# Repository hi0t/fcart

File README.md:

# Open source flash cartridge for FC

**⚠️ This project is currently in active development stage**

## Hardware Features

- **8MB SDRAM** - Single SDRAM module for loading both PRG and CHR data with fast access and execution
- **MachXO2 FPGA** - Main logic implemented in Lattice MachXO2 FPGA
- **ARM processor** - Dedicated ARM processor handles ROM loading from SD card and system management
- **Expansion Audio** - Additional sound support powered by an onboard Op-Amp
- **RTC Battery** - Onboard battery for Real-Time Clock support
- **Simple PCB design** - Circuit design optimized for hand assembly and DIY builds
- **USB programming port** - USB interface for firmware updates

## Software Features

- **Game loading from SD card** - Fast ROM loading and execution directly from SD card storage (supports FAT16, FAT32, and exFAT)
- **In-game menu** - Access save states and return to the main menu without resetting the console
- **Save states** - Save and load game progress at any point during gameplay
- **Battery-backed RAM** - Saving backed RAM to flash storage automatically when entering the in-game menu or resetting the console
- **Alphabetical sorting** - Automatic alphabetical sorting of files and folders in the file browser

## Getting Started

1. **Flash the bootloader**: First, you need to flash the bootloader to the cartridge using the project's [GitHub Pages site](https://hi0t.github.io/fcart/).
2. **Install/Update Firmware**: With the SD card removed, connect the cartridge via USB. It will boot into bootloader mode and appear as a USB drive named `FCART BOOT`. Download the latest `fcart.uf2` firmware file from the [Releases page](https://github.com/hi0t/fcart/releases) and copy it to this drive.
3. **Ready to play**: Insert your SD card with ROMs, plug the cartridge into your console, and it's ready to use!

## Manufacturing (PCB)

**Ordering Specifications:**
- **Thickness:** 1.2 mm
- **Surface Finish:** **ENIG** (Electroless Nickel Immersion Gold) is recommended. While this finish is more expensive than standard HASL, it provides significantly better durability.
- **Edge Connector:** **Gold Fingers** (make sure to specify this option even if ENIG is selected).
- **Gold Fingers Bevel:** **45° Bevel** (Chamfer). This ensures smooth and safe repeated insertions into the console.

**Production Files:**
- 🗺️ [Interactive HTML BOM (iBOM)](https://hi0t.github.io/fcart/board/fcart-ibom.html) - Convenient interactive map for hand assembly.
- 📄 [BOM (CSV)](https://hi0t.github.io/fcart/board/fcart-bom.csv) - Bill of Materials in CSV format (includes DigiKey and LCSC part numbers).
- 📦 [Gerbers & Drills (ZIP)](https://hi0t.github.io/fcart/board/fcart-gerbers.zip) - Ready-to-order manufacturing archive.

## Supported Mappers

| | +0 | +1 | +2 | +3 | +4 | +5 | +6 | +7 | +8 | +9 |
|---|:---:|:---:|:---:|:---:|:---:|:---:|:---:|:---:|:---:|:---:|
| **00** | NROM | MMC1B | UxROM | CNROM | MMC3 | | | AxROM | | |
| **10** | | | | | | | | | | |
| **20** | | VRC4a | VRC2a | VRC2b | VRC6a | VRC4b | VRC6b | VRC4 | | |
| **30** | | | | | | | | | | |
| **40** | | | | | | | | | | |
| **50** | | | | | | | | | | |
| **60** | | | | | | | | | | FME7 |
| **70** | | | | | | | | | | |
| **80** | | | | | | | | | | |
| **90** | | | | | UN1ROM | | | | | |
| **100** | | | | | | | | | | |
| **110** | | | | | | | | | | |
| **120** | | | | | | | | | | |
| **130** | | | | | | | | | | |
| **140** | | | | | | | | | | |
| **150** | | | | | | MMC1A | | | | |
| **160** | | | | | | | | | | |
| **170** | | KS7058 | | | | | | | | |
| **180** | UNROM | | | | | CNROM | | | | |
| **190** | | | | | | | | | | |
| **200** | | | | | | | | | | |
| **210** | | | | | | | | | | |
| **220** | | | | | | | | | | |
| **230** | | | | | | | | | | |
| **240** | | | | | | | | | | |
| **250** | | | | | | | | | | |

## Planned Features

- [ ] **Extended mapper support** - Adding support for a larger number of mappers to increase game compatibility
- [ ] **FDS support** - Support for loading FDS disk images

## Photos

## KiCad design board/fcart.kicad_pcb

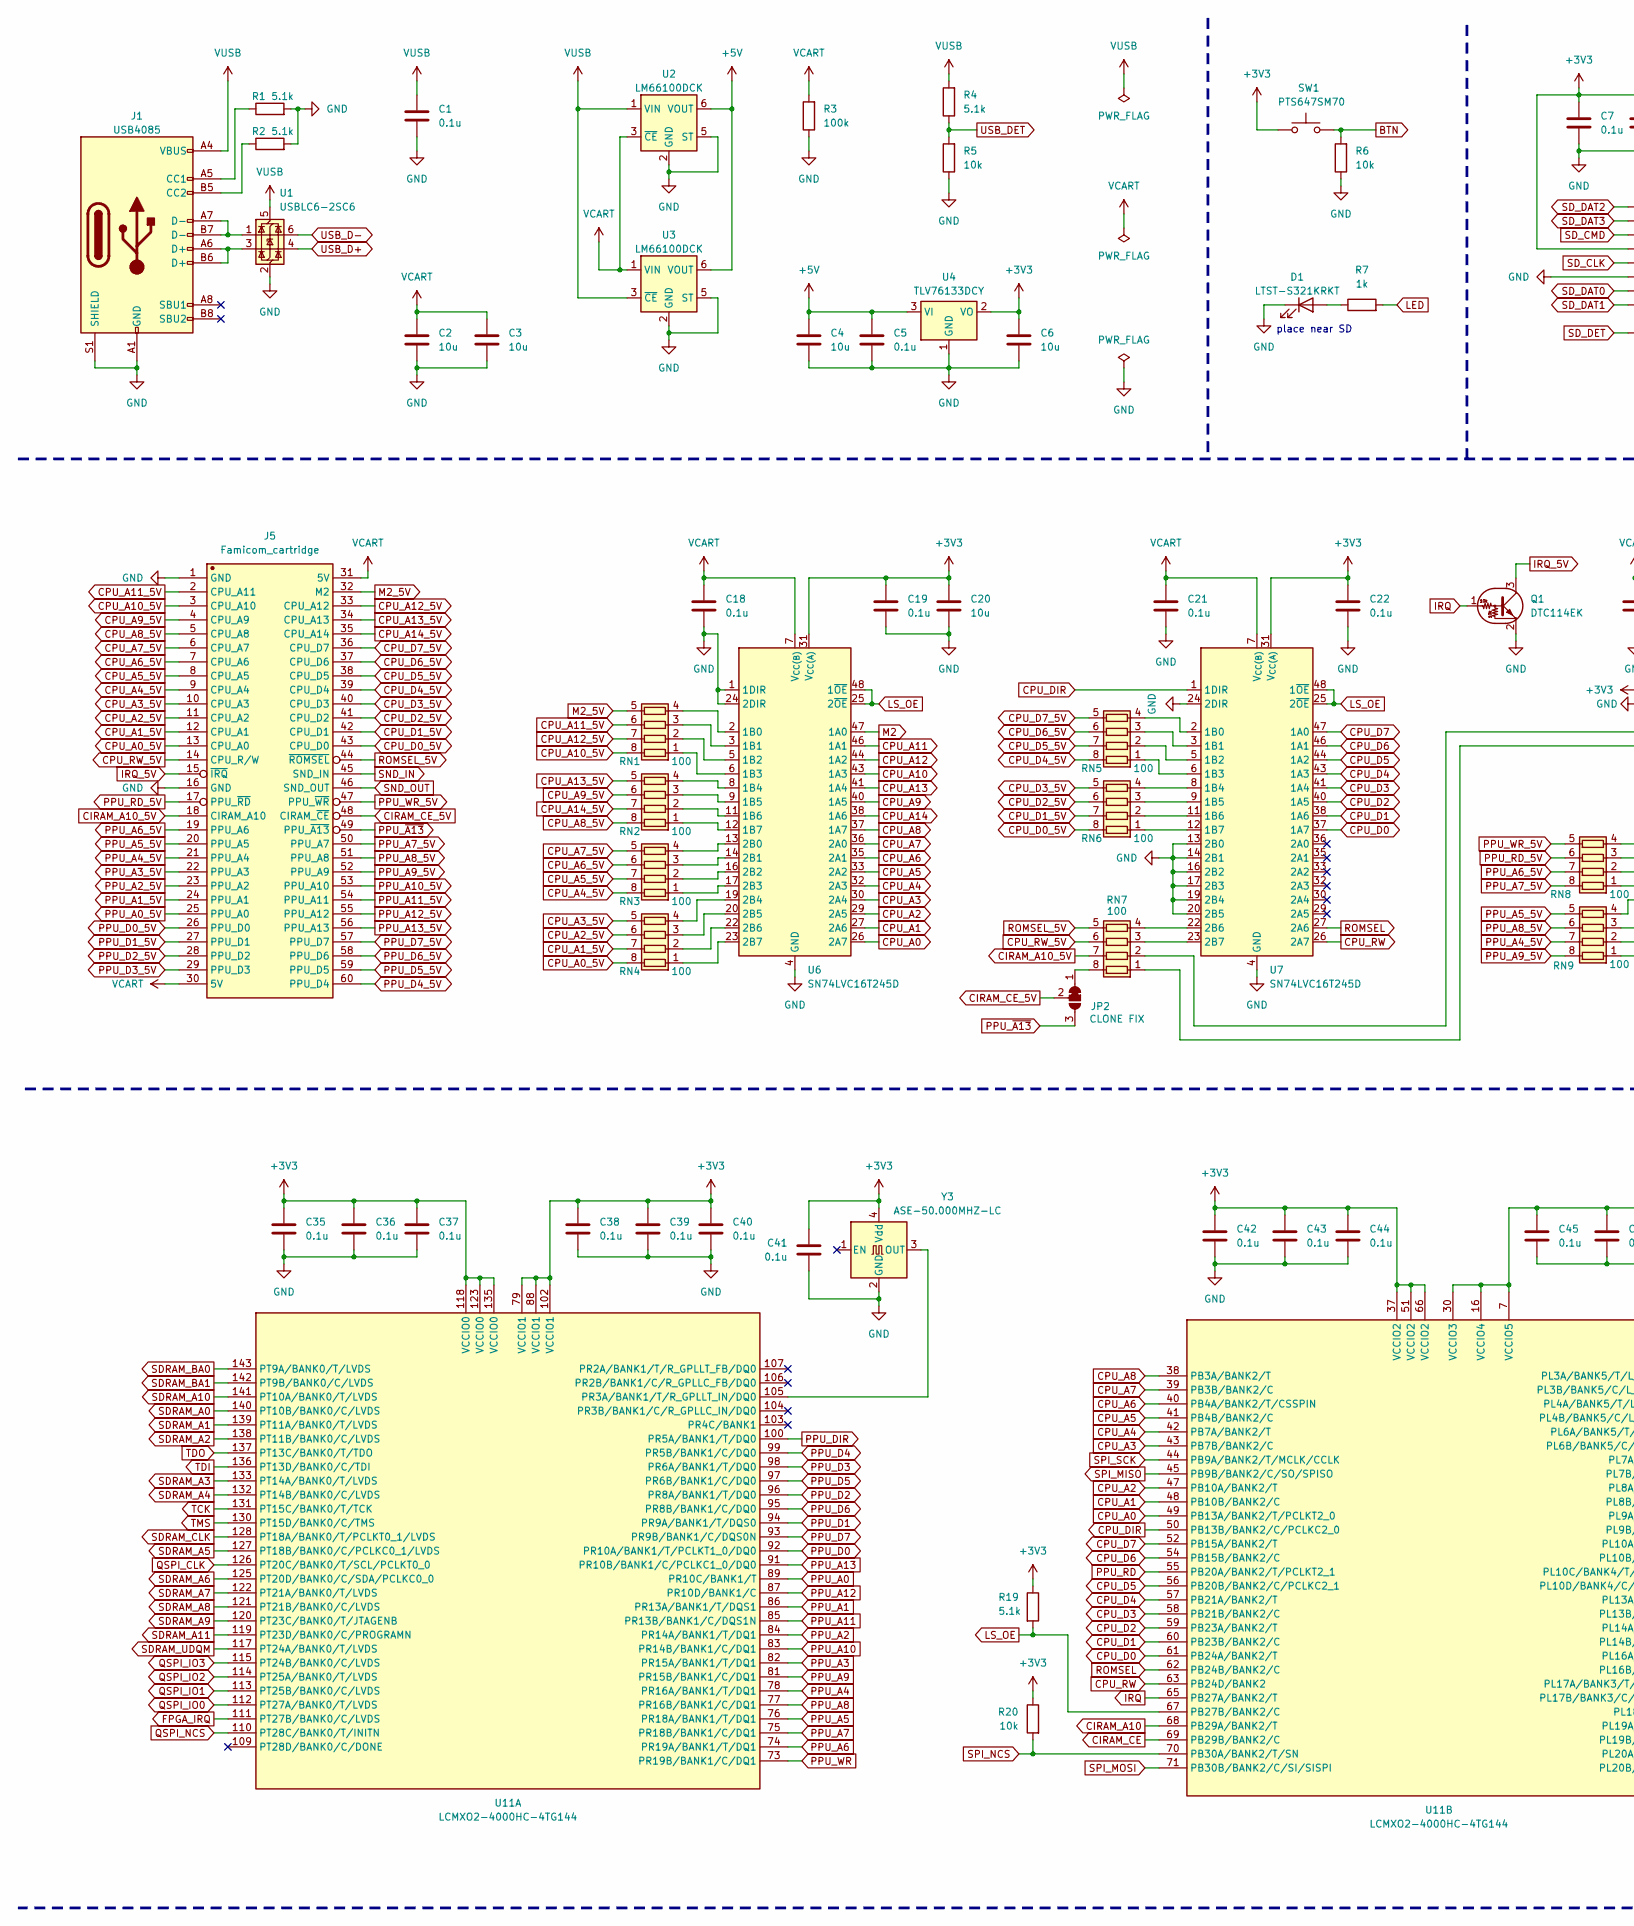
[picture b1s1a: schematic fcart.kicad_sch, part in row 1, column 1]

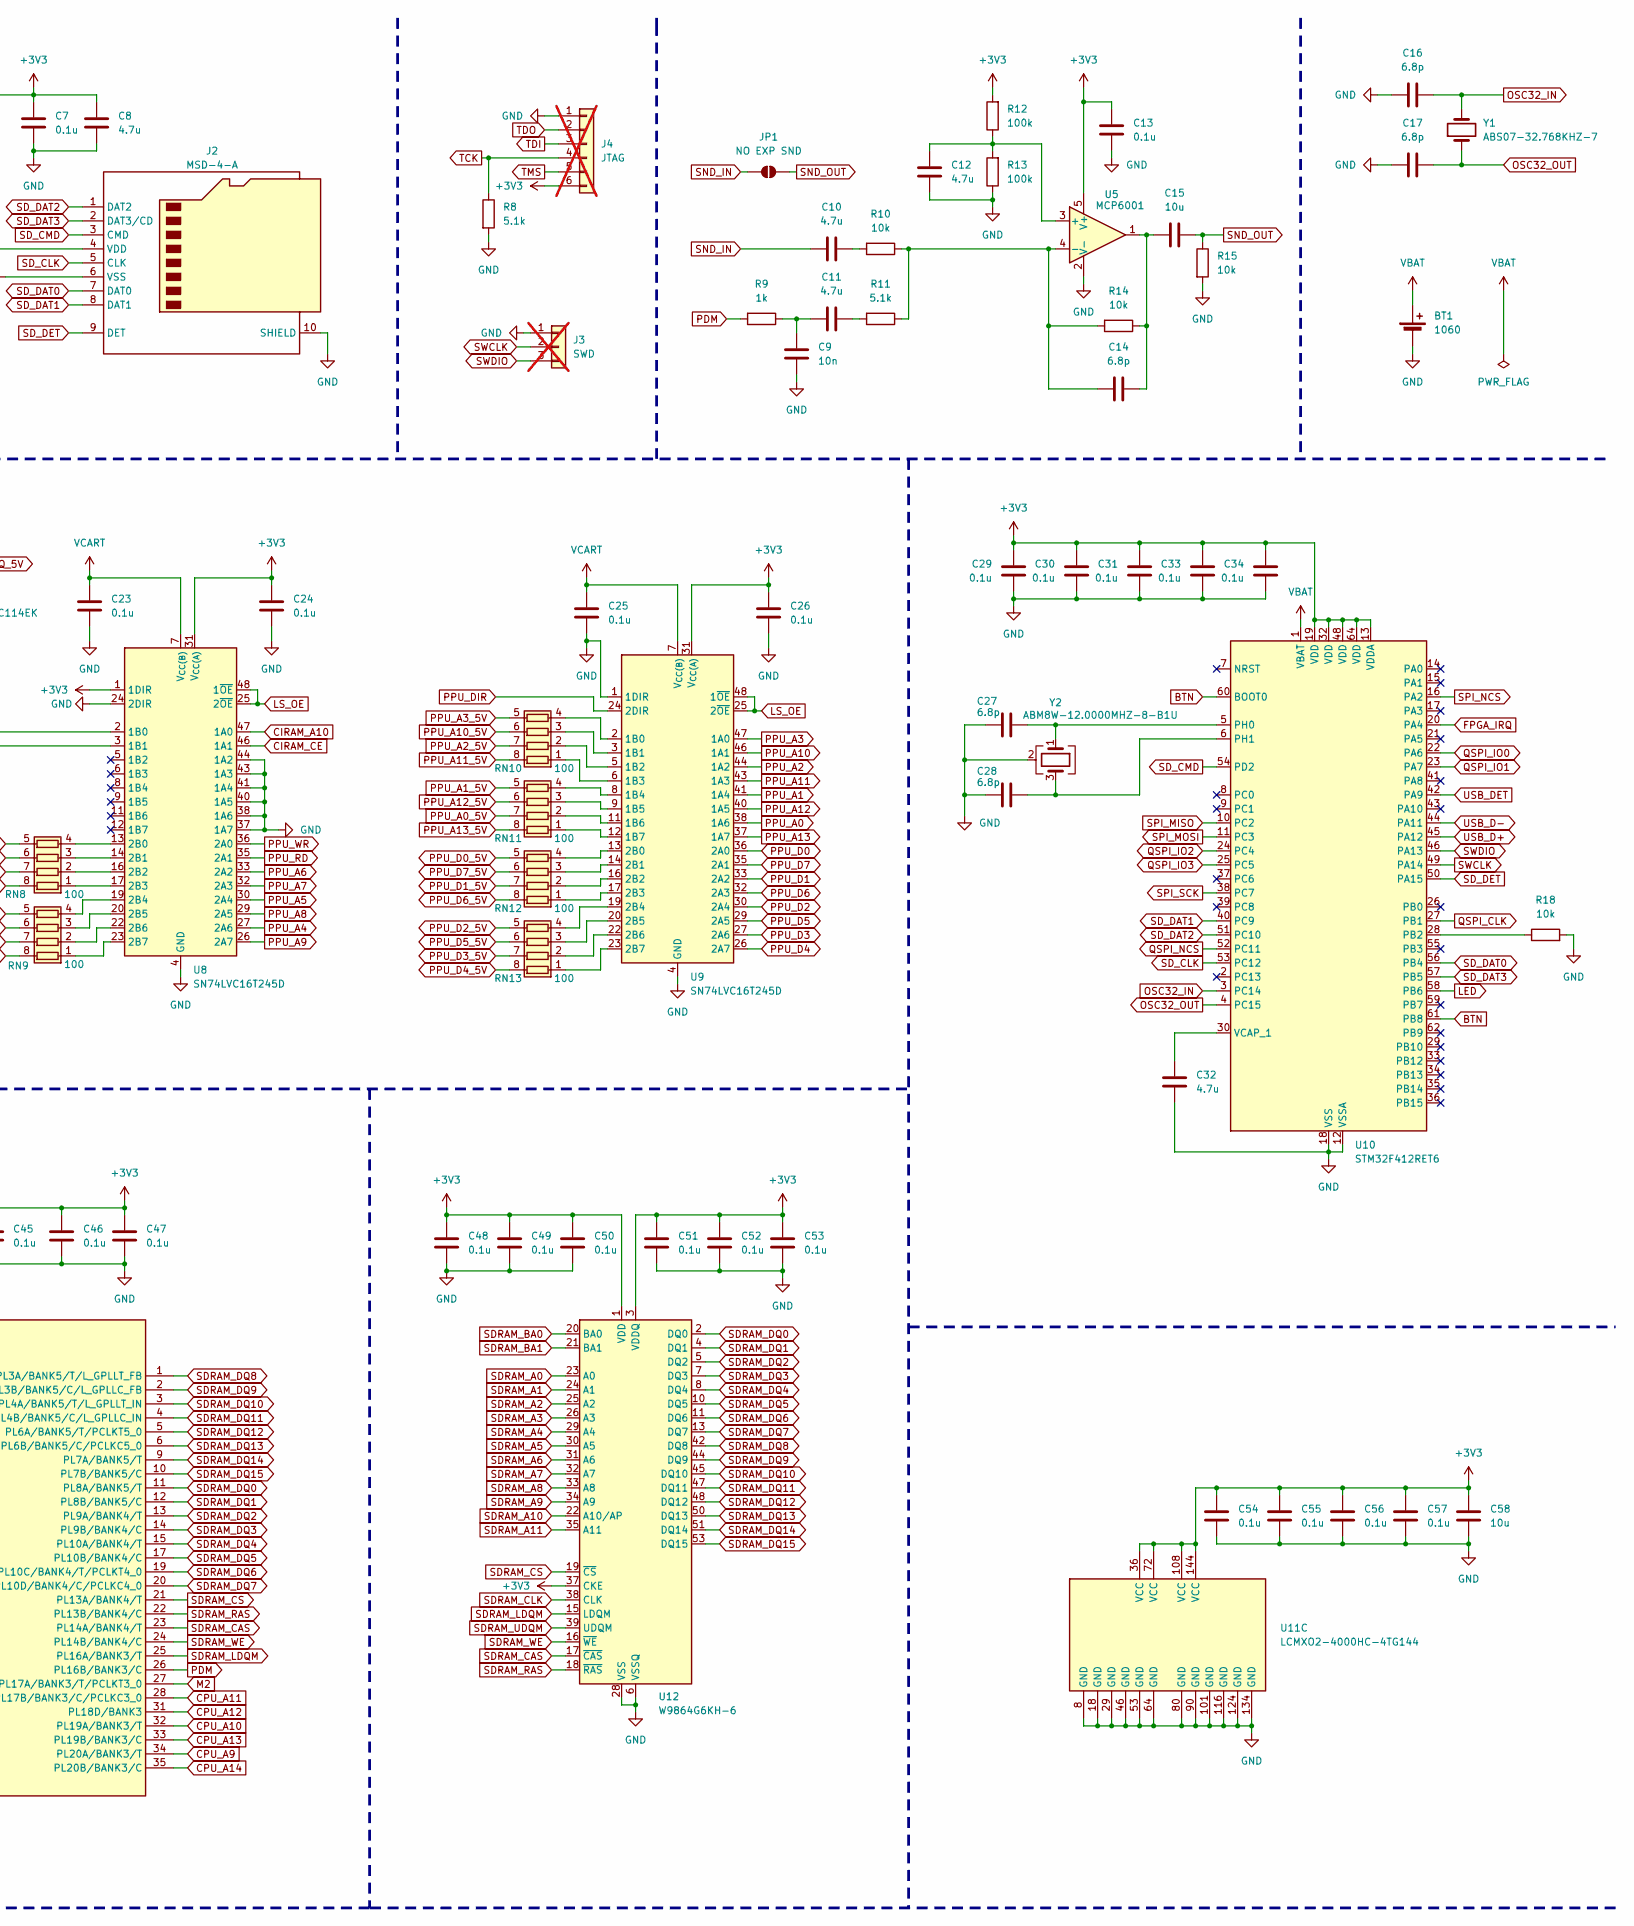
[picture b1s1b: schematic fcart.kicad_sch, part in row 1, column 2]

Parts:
BT1: 1060; BatteryHolder_Keystone_1060_1x2032
C1, C5, C7, C13, C18, C19, C21, C22, C23, C24, C25, C26, C29, C30, C31, C33, C34, C35, C36, C37, C38, C39, C40, C41, C42, C43, C44, C45, C46, C47, C48, C49, C50, C51, C52, C53, C54, C55, C56, C57: 0.1u; C_0805_2012Metric
C2, C3, C4, C6, C15, C20, C58: 10u; C_0805_2012Metric
C8, C10, C11, C12, C32: 4.7u; C_0805_2012Metric
C9: 10n; C_0805_2012Metric
C14, C16, C17, C27, C28: 6.8p; C_0805_2012Metric
D1: LTST-S321KRKT; LED_1208_Horizontal_3210Metric
J1: USB4085; USB_C_Receptacle_GCT_USB4085
J2: MSD-4-A; microSD_HC_Same_Sky_MSD-4-A
J3: SWD; PinHeader_1x03_P2.54mm_Vertical; not fitted
J4: JTAG; PinHeader_1x06_P2.54mm_Vertical; not fitted
J5: Famicom_cartridge; Famicom cartridge pcb
JP1: NO EXP SND; SolderJumper-2_P1.3mm_Open_RoundedPad1.0x1.5mm
JP2: CLONE FIX; SolderJumper-3_P1.3mm_Bridged12_RoundedPad1.0x1.5mm
Q1: DTC114EK; SOT-23-3
R1, R2, R4, R8, R11, R19: 5.1k; R_0805_2012Metric
R3, R12, R13: 100k; R_0805_2012Metric
R5, R6, R10, R14, R15, R18, R20: 10k; R_0805_2012Metric
R7, R9: 1k; R_0805_2012Metric
RN1, RN2, RN3, RN4, RN5, RN6, RN7, RN8, RN9, RN10, RN11, RN12, RN13: 100; R_Array_Convex_4x0603
SW1: PTS647SM70; SW_SPST_PTS647_Sx70
U1: USBLC6-2SC6; SOT-23-6
U2, U3: LM66100DCK; SOT-363_SC-70-6
U4: TLV76133DCY; SOT-223-3_TabPin2
U5: MCP6001; SOT-23-5
U6, U7, U8, U9: SN74LVC16T245D; TSSOP-48_6.1x12.5mm_P0.5mm
U10: STM32F412RET6; LQFP-64_10x10mm_P0.5mm
U11: LCMXO2-4000HC-4TG144; TQFP-144_20x20mm_P0.5mm
U12: W9864G6KH-6; TSOP-II-54_22.2x10.16mm_P0.8mm
Y1: ABS07-32.768KHZ-7; Crystal_SMD_3215-2Pin_3.2x1.5mm
Y2: ABM8W-12.0000MHZ-8-B1U; Crystal_SMD_3225-4Pin_3.2x2.5mm
Y3: ASE-50.000MHZ-LC; Oscillator_SMD_Abracon_ASE-4Pin_3.2x2.5mm

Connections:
+3V3: C6.1, C7.1, C8.1, C13.2, C19.1, C20.1, C22.1, C24.1, C26.1, C29.1, C30.1, C31.1, C33.1, C34.1, C35.1, C36.1, C37.1, C38.1, C39.1, C40.1, C41.1, C42.1, C43.1, C44.1, C45.1, C46.1, C47.1, C48.1, C49.1, C50.1, C51.1, C52.1, C53.1, C54.1, C55.1, C56.1, C57.1, C58.1, J2.4 (VDD), J4.6, R12.2, R19.1, R20.1, SW1.1, U4.2 (VO), U5.5 (V+), U6.31 (V_{CC(A)}), U6.42 (V_{CC(A)}), U7.31 (V_{CC(A)}), U7.42 (V_{CC(A)}), U8.1 (1DIR), U8.31 (V_{CC(A)}), U8.42 (V_{CC(A)}), U9.31 (V_{CC(A)}), U9.42 (V_{CC(A)}), U10.13 (VDDA), U10.19 (VDD), U10.32 (VDD), U10.48 (VDD), U10.64 (VDD), U11.7 (VCCIO5), U11.16 (VCCIO4), U11.30 (VCCIO3), U11.36 (VCC), U11.37 (VCCIO2), U11.51 (VCCIO2), U11.66 (VCCIO2), U11.72 (VCC), U11.79 (VCCIO1), U11.88 (VCCIO1), U11.102 (VCCIO1), U11.108 (VCC), U11.118 (VCCIO0), U11.123 (VCCIO0), U11.135 (VCCIO0), U11.144 (VCC), U12.1 (VDD), U12.3 (VDDQ), U12.9 (VDDQ), U12.14 (VDD), U12.27 (VDD), U12.37 (CKE), U12.43 (VDDQ), U12.49 (VDDQ), Y3.4 (Vdd)
+5V: C4.1, C5.1, U2.6 (VOUT), U3.6 (VOUT), U4.3 (VI)
BTN: R6.2, SW1.2, U10.60 (BOOT0), U10.61 (PB8)
CIRAM_A10: U8.47 (1A0), U11.68 (PB29A/BANK2/T)
CIRAM_A10_5V: J5.18 (CIRAM_A10), RN7.7 (R2.2)
CIRAM_CE: U8.46 (1A1), U11.69 (PB29B/BANK2/C)
CIRAM_CE_5V: J5.48 (CIRAM_~CE), JP2.2 (C)
CPU_A0: U6.26 (2A7), U11.49 (PB13A/BANK2/T/PCLKT2_0)
CPU_A0_5V: J5.13 (CPU_A0), RN4.8 (R1.2)
CPU_A1: U6.27 (2A6), U11.48 (PB10B/BANK2/C)
CPU_A1_5V: J5.12 (CPU_A1), RN4.7 (R2.2)
CPU_A2: U6.29 (2A5), U11.47 (PB10A/BANK2/T)
CPU_A2_5V: J5.11 (CPU_A2), RN4.6 (R3.2)
CPU_A3: U6.30 (2A4), U11.43 (PB7B/BANK2/C)
CPU_A3_5V: J5.10 (CPU_A3), RN4.5 (R4.2)
CPU_A4: U6.32 (2A3), U11.42 (PB7A/BANK2/T)
CPU_A4_5V: J5.9 (CPU_A4), RN3.8 (R1.2)
CPU_A5: U6.33 (2A2), U11.41 (PB4B/BANK2/C)
CPU_A5_5V: J5.8 (CPU_A5), RN3.7 (R2.2)
CPU_A6: U6.35 (2A1), U11.40 (PB4A/BANK2/T/CSSPIN)
CPU_A6_5V: J5.7 (CPU_A6), RN3.6 (R3.2)
CPU_A7: U6.36 (2A0), U11.39 (PB3B/BANK2/C)
CPU_A7_5V: J5.6 (CPU_A7), RN3.5 (R4.2)
CPU_A8: U6.37 (1A7), U11.38 (PB3A/BANK2/T)
CPU_A8_5V: J5.5 (CPU_A8), RN2.8 (R1.2)
CPU_A9: U6.40 (1A5), U11.34 (PL20A/BANK3/T)
CPU_A9_5V: J5.4 (CPU_A9), RN2.6 (R3.2)
CPU_A10: U6.43 (1A3), U11.32 (PL19A/BANK3/T)
CPU_A10_5V: J5.3 (CPU_A10), RN1.8 (R1.2)
CPU_A11: U6.46 (1A1), U11.28 (PL17B/BANK3/C/PCLKC3_0)
CPU_A11_5V: J5.2 (CPU_A11), RN1.6 (R3.2)
CPU_A12: U6.44 (1A2), U11.31 (PL18D/BANK3)
CPU_A12_5V: J5.33 (CPU_A12), RN1.7 (R2.2)
CPU_A13: U6.41 (1A4), U11.33 (PL19B/BANK3/C)
CPU_A13_5V: J5.34 (CPU_A13), RN2.5 (R4.2)
CPU_A14: U6.38 (1A6), U11.35 (PL20B/BANK3/C)
CPU_A14_5V: J5.35 (CPU_A14), RN2.7 (R2.2)
CPU_D0: U7.37 (1A7), U11.61 (PB24A/BANK2/T)
CPU_D0_5V: J5.43 (CPU_D0), RN6.8 (R1.2)
CPU_D1: U7.38 (1A6), U11.60 (PB23B/BANK2/C)
CPU_D1_5V: J5.42 (CPU_D1), RN6.7 (R2.2)
CPU_D2: U7.40 (1A5), U11.59 (PB23A/BANK2/T)
CPU_D2_5V: J5.41 (CPU_D2), RN6.6 (R3.2)
CPU_D3: U7.41 (1A4), U11.58 (PB21B/BANK2/C)
CPU_D3_5V: J5.40 (CPU_D3), RN6.5 (R4.2)
CPU_D4: U7.43 (1A3), U11.57 (PB21A/BANK2/T)
CPU_D4_5V: J5.39 (CPU_D4), RN5.8 (R1.2)
CPU_D5: U7.44 (1A2), U11.56 (PB20B/BANK2/C/PCLKC2_1)
CPU_D5_5V: J5.38 (CPU_D5), RN5.7 (R2.2)
CPU_D6: U7.46 (1A1), U11.54 (PB15B/BANK2/C)
CPU_D6_5V: J5.37 (CPU_D6), RN5.6 (R3.2)
CPU_D7: U7.47 (1A0), U11.52 (PB15A/BANK2/T)
CPU_D7_5V: J5.36 (CPU_D7), RN5.5 (R4.2)
CPU_DIR: U7.1 (1DIR), U11.50 (PB13B/BANK2/C/PCLKC2_0)
CPU_RW: U7.26 (2A7), U11.63 (PB24D/BANK2)
CPU_RW_5V: J5.14 (CPU_R/W), RN7.6 (R3.2)
FPGA_IRQ: U10.20 (PA4), U11.111 (PT27B/BANK0/C/LVDS)
GND: BT1.2 (-), C1.2, C2.2, C3.2, C4.2, C5.2, C6.2, C7.2, C8.2, C9.2, C12.1, C13.1, C16.1, C17.1, C18.2, C19.2, C20.2, C21.2, C22.2, C23.2, C24.2, C25.2, C26.2, C27.1, C28.1, C29.2, C30.2, C31.2, C32.2, C33.2, C34.2, C35.2, C36.2, C37.2, C38.2, C39.2, C40.2, C41.2, C42.2, C43.2, C44.2, C45.2, C46.2, C47.2, C48.2, C49.2, C50.2, C51.2, C52.2, C53.2, C54.2, C55.2, C56.2, C57.2, C58.2, D1.1 (K), J1.A1 (GND), J1.A12 (GND), J1.B1 (GND), J1.B12 (GND), J1.S1 (SHIELD), J2.6 (VSS), J2.10 (SHIELD), J3.1, J4.1, J5.1 (GND), J5.16 (GND), Q1.2 (E), R1.2, R2.2, R3.1, R5.1, R6.1, R8.2, R13.1, R15.2, R18.2, U1.2 (GND), U2.2 (GND), U2.5 (ST), U3.2 (GND), U3.5 (ST), U4.1 (GND), U5.2 (V-), U6.1 (1DIR), U6.4 (GND), U6.10 (GND), U6.15 (GND), U6.21 (GND), U6.24 (2DIR), U6.28 (GND), U6.34 (GND), U6.39 (GND), U6.45 (GND), U7.4 (GND), U7.10 (GND), U7.13 (2B0), U7.14 (2B1), U7.15 (GND), U7.16 (2B2), U7.17 (2B3), U7.19 (2B4), U7.20 (2B5), U7.21 (GND), U7.24 (2DIR), U7.28 (GND), U7.34 (GND), U7.39 (GND), U7.45 (GND), U8.4 (GND), U8.10 (GND), U8.15 (GND), U8.21 (GND), U8.24 (2DIR), U8.28 (GND), U8.34 (GND), U8.37 (1A7), U8.38 (1A6), U8.39 (GND), U8.40 (1A5), U8.41 (1A4), U8.43 (1A3), U8.44 (1A2), U8.45 (GND), U9.1 (1DIR), U9.4 (GND), U9.10 (GND), U9.15 (GND), U9.21 (GND), U9.28 (GND), U9.34 (GND), U9.39 (GND), U9.45 (GND), U10.12 (VSSA), U10.18 (VSS), U10.31 (VSS), U10.47 (VSS), U10.63 (VSS), U11.8 (GND), U11.18 (GND), U11.29 (GND), U11.46 (GND), U11.53 (GND), U11.64 (GND), U11.80 (GND), U11.90 (GND), U11.101 (GND), U11.116 (GND), U11.124 (GND), U11.134 (GND), U12.6 (VSSQ), U12.12 (VSSQ), U12.28 (VSS), U12.41 (VSS), U12.46 (VSSQ), U12.52 (VSSQ), U12.54 (VSS), Y2.2 (G), Y2.4 (G), Y3.2 (GND)
IRQ: Q1.1 (B), U11.65 (PB27A/BANK2/T)
IRQ_5V: J5.15 (~IRQ), Q1.3 (C)
LED: R7.2, U10.58 (PB6)
LS_OE: R19.2, U6.25 (2~OE), U6.48 (1~OE), U7.25 (2~OE), U7.48 (1~OE), U8.25 (2~OE), U8.48 (1~OE), U9.25 (2~OE), U9.48 (1~OE), U11.67 (PB27B/BANK2/C)
M2: U6.47 (1A0), U11.27 (PL17A/BANK3/T/PCLKT3_0)
M2_5V: J5.32 (M2), RN1.5 (R4.2)
unnamed: C10.2, R10.2
unnamed: C9.1, C11.1, R9.1
unnamed: C11.2, R11.2
unnamed: C14.2, C15.1, R14.1, U5.1
unnamed: D1.2 (A), R7.1
unnamed: J1.A5 (CC1), R1.1
unnamed: J1.B5 (CC2), R2.1
unnamed: J1.A6 (D+), J1.B6 (D+), U1.3 (I/O2)
unnamed: J1.A7 (D-), J1.B7 (D-), U1.1 (I/O1)
unnamed: JP2.1 (A), RN7.8 (R1.2)
unnamed: RN1.1 (R1.1), U6.6 (1B3)
unnamed: RN1.2 (R2.1), U6.5 (1B2)
unnamed: RN1.3 (R3.1), U6.3 (1B1)
unnamed: RN1.4 (R4.1), U6.2 (1B0)
unnamed: RN2.1 (R1.1), U6.12 (1B7)
unnamed: RN2.2 (R2.1), U6.11 (1B6)
unnamed: RN2.3 (R3.1), U6.9 (1B5)
unnamed: RN2.4 (R4.1), U6.8 (1B4)
unnamed: RN3.1 (R1.1), U6.17 (2B3)
unnamed: RN3.2 (R2.1), U6.16 (2B2)
unnamed: RN3.3 (R3.1), U6.14 (2B1)
unnamed: RN3.4 (R4.1), U6.13 (2B0)
unnamed: RN4.1 (R1.1), U6.23 (2B7)
unnamed: RN4.2 (R2.1), U6.22 (2B6)
unnamed: RN4.3 (R3.1), U6.20 (2B5)
unnamed: RN4.4 (R4.1), U6.19 (2B4)
unnamed: RN5.1 (R1.1), U7.6 (1B3)
unnamed: RN5.2 (R2.1), U7.5 (1B2)
unnamed: RN5.3 (R3.1), U7.3 (1B1)
unnamed: RN5.4 (R4.1), U7.2 (1B0)
unnamed: RN6.1 (R1.1), U7.12 (1B7)
unnamed: RN6.2 (R2.1), U7.11 (1B6)
unnamed: RN6.3 (R3.1), U7.9 (1B5)
unnamed: RN6.4 (R4.1), U7.8 (1B4)
unnamed: RN7.1 (R1.1), U8.3 (1B1)
unnamed: RN7.2 (R2.1), U8.2 (1B0)
unnamed: RN7.3 (R3.1), U7.23 (2B7)
unnamed: RN7.4 (R4.1), U7.22 (2B6)
unnamed: RN8.1 (R1.1), U8.17 (2B3)
unnamed: RN8.2 (R2.1), U8.16 (2B2)
unnamed: RN8.3 (R3.1), U8.14 (2B1)
unnamed: RN8.4 (R4.1), U8.13 (2B0)
unnamed: RN9.1 (R1.1), U8.23 (2B7)
unnamed: RN9.2 (R2.1), U8.22 (2B6)
unnamed: RN9.3 (R3.1), U8.20 (2B5)
unnamed: RN9.4 (R4.1), U8.19 (2B4)
unnamed: RN10.1 (R1.1), U9.6 (1B3)
unnamed: RN10.2 (R2.1), U9.5 (1B2)
unnamed: RN10.3 (R3.1), U9.3 (1B1)
unnamed: RN10.4 (R4.1), U9.2 (1B0)
unnamed: RN11.1 (R1.1), U9.12 (1B7)
unnamed: RN11.2 (R2.1), U9.11 (1B6)
unnamed: RN11.3 (R3.1), U9.9 (1B5)
unnamed: RN11.4 (R4.1), U9.8 (1B4)
unnamed: RN12.1 (R1.1), U9.17 (2B3)
unnamed: RN12.2 (R2.1), U9.16 (2B2)
unnamed: RN12.3 (R3.1), U9.14 (2B1)
unnamed: RN12.4 (R4.1), U9.13 (2B0)
unnamed: RN13.1 (R1.1), U9.23 (2B7)
unnamed: RN13.2 (R2.1), U9.22 (2B6)
unnamed: RN13.3 (R3.1), U9.20 (2B5)
unnamed: RN13.4 (R4.1), U9.19 (2B4)
unnamed: C12.2, R12.1, R13.2, U5.3 (+)
unnamed: C14.1, R10.1, R11.1, R14.2, U5.4 (-)
unnamed: R18.1, U10.28 (PB2)
unnamed: C27.2, U10.5 (PH0), Y2.1
unnamed: C28.2, U10.6 (PH1), Y2.3
unnamed: C32.1, U10.30 (VCAP_1)
unnamed: U11.105 (PR3A/BANK1/T/R_GPLLT_IN/DQ0), Y3.3 (OUT)
OSC32_IN: C16.2, U10.3 (PC14), Y1.2
OSC32_OUT: C17.2, U10.4 (PC15), Y1.1
PDM: R9.2, U11.26 (PL16B/BANK3/C)
PPU_A0: U9.38 (1A6), U11.89 (PR10C/BANK1/T)
PPU_A0_5V: J5.25 (PPU_A0), RN11.7 (R2.2)
PPU_A1: U9.41 (1A4), U11.86 (PR13A/BANK1/T/DQS1)
PPU_A1_5V: J5.24 (PPU_A1), RN11.5 (R4.2)
PPU_A2: U9.44 (1A2), U11.84 (PR14A/BANK1/T/DQ1)
PPU_A2_5V: J5.23 (PPU_A2), RN10.7 (R2.2)
PPU_A3: U9.47 (1A0), U11.82 (PR15A/BANK1/T/DQ1)
PPU_A3_5V: J5.22 (PPU_A3), RN10.5 (R4.2)
PPU_A4: U8.27 (2A6), U11.78 (PR16A/BANK1/T/DQ1)
PPU_A4_5V: J5.21 (PPU_A4), RN9.7 (R2.2)
PPU_A5: U8.30 (2A4), U11.76 (PR18A/BANK1/T/DQ1)
PPU_A5_5V: J5.20 (PPU_A5), RN9.5 (R4.2)
PPU_A6: U8.33 (2A2), U11.74 (PR19A/BANK1/T/DQ1)
PPU_A6_5V: J5.19 (PPU_A6), RN8.7 (R2.2)
PPU_A7: U8.32 (2A3), U11.75 (PR18B/BANK1/C/DQ1)
PPU_A7_5V: J5.50 (PPU_A7), RN8.8 (R1.2)
PPU_A8: U8.29 (2A5), U11.77 (PR16B/BANK1/C/DQ1)
PPU_A8_5V: J5.51 (PPU_A8), RN9.6 (R3.2)
PPU_A9: U8.26 (2A7), U11.81 (PR15B/BANK1/C/DQ1)
PPU_A9_5V: J5.52 (PPU_A9), RN9.8 (R1.2)
PPU_A10: U9.46 (1A1), U11.83 (PR14B/BANK1/C/DQ1)
PPU_A10_5V: J5.53 (PPU_A10), RN10.6 (R3.2)
PPU_A11: U9.43 (1A3), U11.85 (PR13B/BANK1/C/DQS1N)
PPU_A11_5V: J5.54 (PPU_A11), RN10.8 (R1.2)
PPU_A12: U9.40 (1A5), U11.87 (PR10D/BANK1/C)
PPU_A12_5V: J5.55 (PPU_A12), RN11.6 (R3.2)
PPU_A13: U9.37 (1A7), U11.91 (PR10B/BANK1/C/PCLKC1_0/DQ0)
PPU_A13_5V: J5.56 (PPU_A13), RN11.8 (R1.2)
PPU_D0: U9.36 (2A0), U11.92 (PR10A/BANK1/T/PCLKT1_0/DQ0)
PPU_D0_5V: J5.26 (PPU_D0), RN12.5 (R4.2)
PPU_D1: U9.33 (2A2), U11.94 (PR9A/BANK1/T/DQS0)
PPU_D1_5V: J5.27 (PPU_D1), RN12.7 (R2.2)
PPU_D2: U9.30 (2A4), U11.96 (PR8A/BANK1/T/DQ0)
PPU_D2_5V: J5.28 (PPU_D2), RN13.5 (R4.2)
PPU_D3: U9.27 (2A6), U11.98 (PR6A/BANK1/T/DQ0)
PPU_D3_5V: J5.29 (PPU_D3), RN13.7 (R2.2)
PPU_D4: U9.26 (2A7), U11.99 (PR5B/BANK1/C/DQ0)
PPU_D4_5V: J5.60 (PPU_D4), RN13.8 (R1.2)
PPU_D5: U9.29 (2A5), U11.97 (PR6B/BANK1/C/DQ0)
PPU_D5_5V: J5.59 (PPU_D5), RN13.6 (R3.2)
PPU_D6: U9.32 (2A3), U11.95 (PR8B/BANK1/C/DQ0)
PPU_D6_5V: J5.58 (PPU_D6), RN12.8 (R1.2)
PPU_D7: U9.35 (2A1), U11.93 (PR9B/BANK1/C/DQS0N)
PPU_D7_5V: J5.57 (PPU_D7), RN12.6 (R3.2)
PPU_DIR: U9.24 (2DIR), U11.100 (PR5A/BANK1/T/DQ0)
PPU_RD: U8.35 (2A1), U11.55 (PB20A/BANK2/T/PCLKT2_1)
PPU_RD_5V: J5.17 (PPU_~RD), RN8.6 (R3.2)
PPU_WR: U8.36 (2A0), U11.73 (PR19B/BANK1/C/DQ1)
PPU_WR_5V: J5.47 (PPU_~WR), RN8.5 (R4.2)
PPU_~A13: J5.49 (PPU_~A13), JP2.3 (B)
QSPI_CLK: U10.27 (PB1), U11.126 (PT20C/BANK0/T/SCL/PCLKT0_0)
QSPI_IO0: U10.22 (PA6), U11.112 (PT27A/BANK0/T/LVDS)
QSPI_IO1: U10.23 (PA7), U11.113 (PT25B/BANK0/C/LVDS)
QSPI_IO2: U10.24 (PC4), U11.114 (PT25A/BANK0/T/LVDS)
QSPI_IO3: U10.25 (PC5), U11.115 (PT24B/BANK0/C/LVDS)
QSPI_NCS: U10.52 (PC11), U11.110 (PT28C/BANK0/T/INITN)
ROMSEL: U7.27 (2A6), U11.62 (PB24B/BANK2/C)
ROMSEL_5V: J5.44 (~ROMSEL), RN7.5 (R4.2)
SDRAM_A0: U11.140 (PT10B/BANK0/C/LVDS), U12.23 (A0)
SDRAM_A1: U11.139 (PT11A/BANK0/T/LVDS), U12.24 (A1)
SDRAM_A2: U11.138 (PT11B/BANK0/C/LVDS), U12.25 (A2)
SDRAM_A3: U11.133 (PT14A/BANK0/T/LVDS), U12.26 (A3)
SDRAM_A4: U11.132 (PT14B/BANK0/C/LVDS), U12.29 (A4)
SDRAM_A5: U11.127 (PT18B/BANK0/C/PCLKC0_1/LVDS), U12.30 (A5)
SDRAM_A6: U11.125 (PT20D/BANK0/C/SDA/PCLKC0_0), U12.31 (A6)
SDRAM_A7: U11.122 (PT21A/BANK0/T/LVDS), U12.32 (A7)
SDRAM_A8: U11.121 (PT21B/BANK0/C/LVDS), U12.33 (A8)
SDRAM_A9: U11.120 (PT23C/BANK0/T/JTAGENB), U12.34 (A9)
SDRAM_A10: U11.141 (PT10A/BANK0/T/LVDS), U12.22 (A10/AP)
SDRAM_A11: U11.119 (PT23D/BANK0/C/PROGRAMN), U12.35 (A11)
SDRAM_BA0: U11.143 (PT9A/BANK0/T/LVDS), U12.20 (BA0)
SDRAM_BA1: U11.142 (PT9B/BANK0/C/LVDS), U12.21 (BA1)
SDRAM_CAS: U11.23 (PL14A/BANK4/T), U12.17 (~CAS)
SDRAM_CLK: U11.128 (PT18A/BANK0/T/PCLKT0_1/LVDS), U12.38 (CLK)
SDRAM_CS: U11.21 (PL13A/BANK4/T), U12.19 (~CS)
SDRAM_DQ0: U11.11 (PL8A/BANK5/T), U12.2 (DQ0)
SDRAM_DQ1: U11.12 (PL8B/BANK5/C), U12.4 (DQ1)
SDRAM_DQ2: U11.13 (PL9A/BANK4/T), U12.5 (DQ2)
SDRAM_DQ3: U11.14 (PL9B/BANK4/C), U12.7 (DQ3)
SDRAM_DQ4: U11.15 (PL10A/BANK4/T), U12.8 (DQ4)
SDRAM_DQ5: U11.17 (PL10B/BANK4/C), U12.10 (DQ5)
SDRAM_DQ6: U11.19 (PL10C/BANK4/T/PCLKT4_0), U12.11 (DQ6)
SDRAM_DQ7: U11.20 (PL10D/BANK4/C/PCLKC4_0), U12.13 (DQ7)
SDRAM_DQ8: U11.1 (PL3A/BANK5/T/L_GPLLT_FB), U12.42 (DQ8)
SDRAM_DQ9: U11.2 (PL3B/BANK5/C/L_GPLLC_FB), U12.44 (DQ9)
SDRAM_DQ10: U11.3 (PL4A/BANK5/T/L_GPLLT_IN), U12.45 (DQ10)
SDRAM_DQ11: U11.4 (PL4B/BANK5/C/L_GPLLC_IN), U12.47 (DQ11)
SDRAM_DQ12: U11.5 (PL6A/BANK5/T/PCLKT5_0), U12.48 (DQ12)
SDRAM_DQ13: U11.6 (PL6B/BANK5/C/PCLKC5_0), U12.50 (DQ13)
SDRAM_DQ14: U11.9 (PL7A/BANK5/T), U12.51 (DQ14)
SDRAM_DQ15: U11.10 (PL7B/BANK5/C), U12.53 (DQ15)
SDRAM_LDQM: U11.25 (PL16A/BANK3/T), U12.15 (LDQM)
SDRAM_RAS: U11.22 (PL13B/BANK4/C), U12.18 (~RAS)
SDRAM_UDQM: U11.117 (PT24A/BANK0/T/LVDS), U12.39 (UDQM)
SDRAM_WE: U11.24 (PL14B/BANK4/C), U12.16 (~WE)
SD_CLK: J2.5 (CLK), U10.53 (PC12)
SD_CMD: J2.3 (CMD), U10.54 (PD2)
SD_DAT0: J2.7 (DAT0), U10.56 (PB4)
SD_DAT1: J2.8 (DAT1), U10.40 (PC9)
SD_DAT2: J2.1 (DAT2), U10.51 (PC10)
SD_DAT3: J2.2 (DAT3/CD), U10.57 (PB5)
SD_DET: J2.9 (DET), U10.50 (PA15)
SND_IN: C10.1, J5.45 (SND_IN), JP1.1 (A)
SND_OUT: C15.2, J5.46 (SND_OUT), JP1.2 (B), R15.1
SPI_MISO: U10.10 (PC2), U11.45 (PB9B/BANK2/C/SO/SPISO)
SPI_MOSI: U10.11 (PC3), U11.71 (PB30B/BANK2/C/SI/SISPI)
SPI_NCS: R20.2, U10.16 (PA2), U11.70 (PB30A/BANK2/T/SN)
SPI_SCK: U10.38 (PC7), U11.44 (PB9A/BANK2/T/MCLK/CCLK)
SWCLK: J3.2, U10.49 (PA14)
SWDIO: J3.3, U10.46 (PA13)
TCK: J4.4, R8.1, U11.131 (PT15C/BANK0/T/TCK)
TDI: J4.3, U11.136 (PT13D/BANK0/C/TDI)
TDO: J4.2, U11.137 (PT13C/BANK0/T/TDO)
TMS: J4.5, U11.130 (PT15D/BANK0/C/TMS)
USB_D+: U1.4 (I/O2), U10.45 (PA12)
USB_D-: U1.6 (I/O1), U10.44 (PA11)
USB_DET: R4.1, R5.2, U10.42 (PA9)
VBAT: BT1.1 (+), U10.1 (VBAT)
VCART: C2.1, C3.1, C18.1, C21.1, C23.1, C25.1, J5.30 (5V), J5.31 (5V), R3.2, U2.3 (~CE), U3.1 (VIN), U6.7 (V_{CC(B)}), U6.18 (V_{CC(B)}), U7.7 (V_{CC(B)}), U7.18 (V_{CC(B)}), U8.7 (V_{CC(B)}), U8.18 (V_{CC(B)}), U9.7 (V_{CC(B)}), U9.18 (V_{CC(B)})
VUSB: C1.1, J1.A4 (VBUS), J1.A9 (VBUS), J1.B4 (VBUS), J1.B9 (VBUS), R4.2, U1.5 (VBUS), U2.1 (VIN), U3.3 (~CE)

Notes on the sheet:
place near SD

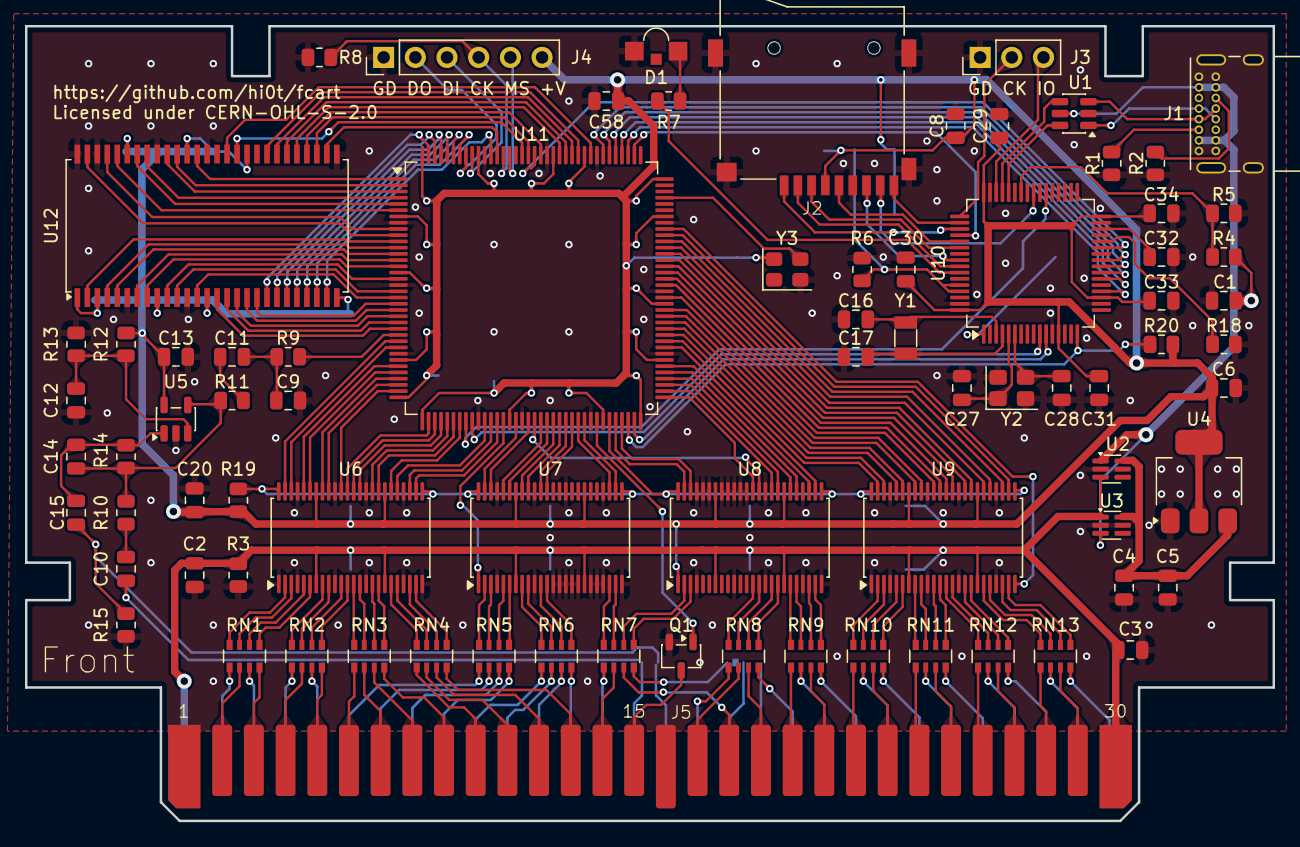
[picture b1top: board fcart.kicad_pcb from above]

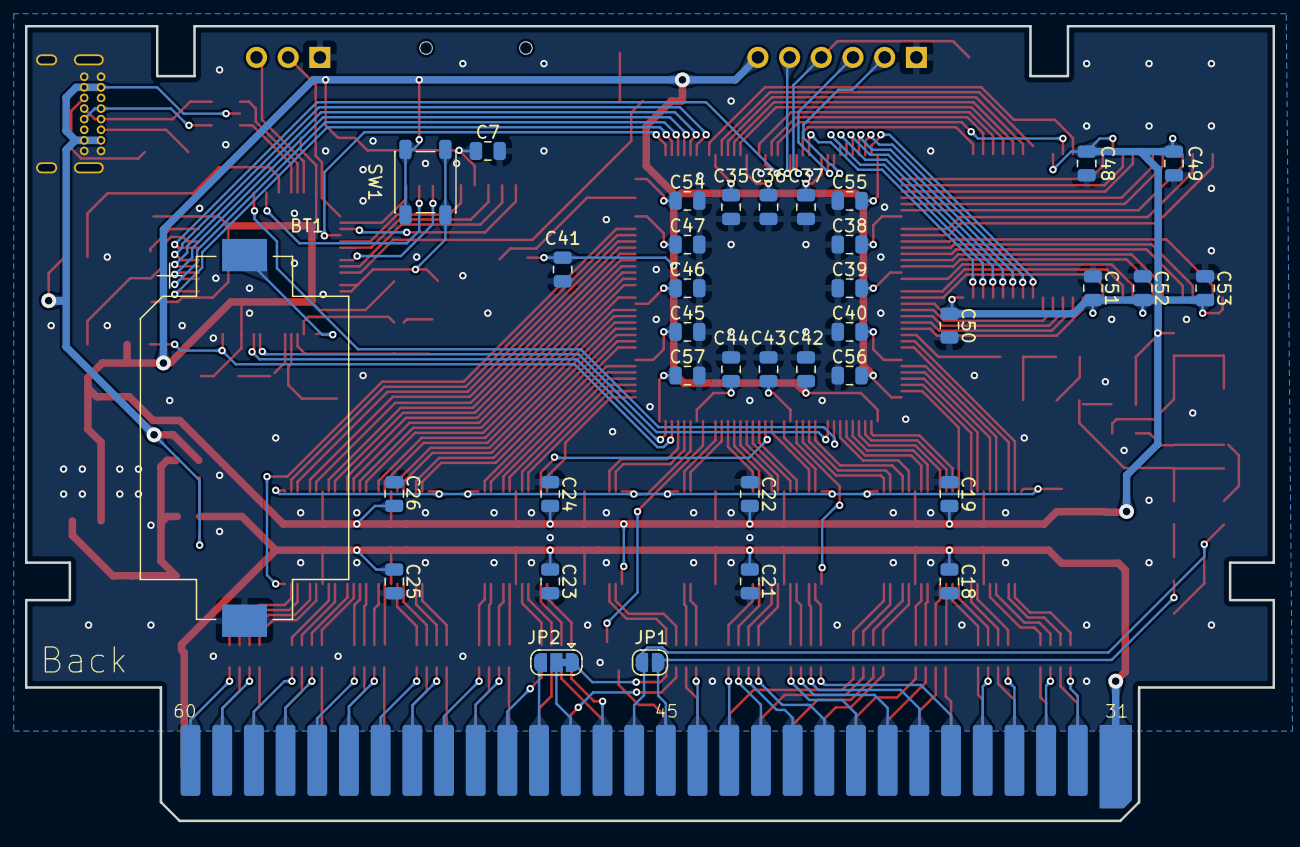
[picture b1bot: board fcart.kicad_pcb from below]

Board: 2 copper layers, 100.0 x 63.7 mm, 115 parts (36 on the bottom side), 256 nets.

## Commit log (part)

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2024-06-07 basic implementation of reading from an SD card
2024-06-08 add error processing
2024-06-08 SD writing support
2024-06-08 add sd card speed test
2024-06-08 add fatfs rtc
2024-06-11 add board defenition
2024-06-25 sdio support
2024-06-26 fix spi multiblock read
2024-06-26 sdio: init dma write channel only once
2024-06-26 sdio: use dma to respond to commands
2024-07-03 fpga: implement sdio command interface
2024-07-23 implement of sdram
2024-07-26 simple emulation
2024-08-01 load rom from sd
2024-08-04 more accurate RAM cycle count
2024-08-09 sdram stabilization
2024-08-16 parallel reading from sdram
2024-08-17 Flexible PPU latching
2024-08-17 generation serial flash
2024-08-18 Simplifying the capture of the PPU address
2024-09-02 fpga flash
2024-09-07 parallel reading from ram
2024-09-17 initial
2025-02-22 add schematic
2025-02-23 switch to stm32
2025-02-24 open edge connectors
2025-02-24 added restrictive zones
2025-02-24 add vbat sensor
2025-02-24 3D models correction
2025-02-27 initital qspi support
2025-02-28 fixes to some tracks
2025-03-01 switch to meson
2025-03-02 separate stm32 libraries
2025-03-03 add logging
2025-03-04 add sdio
2025-03-04 wextra
2025-03-04 add rtc
2025-03-04 add qspi
2025-03-13 switch to lattice
2025-03-14 update pcb holes
2025-03-18 add hw qspi
2025-03-19 add sdram
2025-03-22 implement of api for writing in sdram
2025-03-27 optimize for native board
2025-03-31 loading roms from sdram
2025-04-05 Switch to fpga MAX10
2025-04-27 switch mcu to max 10 board
2025-05-02 loading roms by spi
2025-05-03 interaction with flash memory
2025-05-05 add memtest
2025-05-05 request to memory by pulse
2025-05-07 early reading chr
2025-05-09 implement of jtag program
2025-05-11 New board design based on MachXO2
2025-05-16 rtl design for MachXO2
2025-05-17 reconfig of mcu for a new board
2025-05-26 reduce sdram counter size
2025-05-29 fifo layout optimization
2025-05-29 Stabilization of PPU address by gray code
2025-05-31 take into account ppu offset
2025-08-10 docker build
2025-08-23 basic implementation of mappers
2025-08-23 add cnrom mapper
2025-08-24 add mmc1 mapper
2025-08-31 fixed read/write window qspi
2025-09-02 introduce loader
2025-09-04 loader: simple graphics
2025-09-07 Double buffering graphics
2025-09-10 interaction with joypad
2025-09-10 fix license
2025-09-14 add readme
2025-09-14 directory support
2025-09-30 launch roms from ui
2025-09-30 cpu reset detection
2025-10-01 add summary during synthesis
2025-10-04 sync loader with mcu
2025-10-05 rename loader
2025-10-05 double buffering when writing to FPGA
2025-10-06 fix unsized literals
2025-10-10 simplification of reset
2025-10-10 address comparison optimization
2025-10-11 synchronous QSPI
2025-10-11 switch to synchronous FIFO
2025-10-11 Switch qspi api to synchronous fifo
2025-12-19 remove unused variables
2025-12-19 add api tests
2025-12-31 reading from sdram via qspi
2025-12-31 some fpga api optimizations
2026-01-01 simplify reading of directories
2026-01-01 remove stdbool
2026-01-02 sort files in sdram
2026-01-02 remove sdram ack
2026-01-03 fetch screen list from sdram
2026-01-03 fix qspi timings
2026-01-04 sort with caching of file list
2026-01-04 fix initial boot
2026-01-06 implementation of sound dac
2026-01-10 implementation of VRC6
2026-01-11 add web flasher
2026-01-11 implement bootloader
2026-01-12 add basic USB support
2026-01-12 configurable CDC interface
2026-01-12 add build option for SD filesystem
2026-01-12 remove HAL PCD dependency
2026-01-13 Implement UF2 flashing capabilities
2026-01-13 Connect SDIO to USB
2026-01-13 Add FPGA configuration support
2026-01-13 Combine HW and SW build steps
2026-01-14 Add versioning support
2026-01-14 Add soft USB disconnect
2026-01-14 More accurate ROM launch tracking
2026-01-14 Extra check for firmware presence
2026-01-15 Refactor control flow in reset loop
2026-01-15 PCB: route USB VBUS signal
2026-01-16 add WRAM/SRAM support
2026-01-16 Trigger WRAM flush to SD on console reset
2026-01-16 Add AxROM mapper implementation
2026-01-17 Implement joypad snooping
2026-01-19 Implement initial in-game menu
2026-01-20 Use async FIFO for QSPI buffering
2026-01-21 feat(api): integrate async FIFO
2026-01-23 Stabilize QSPI read operation
2026-01-23 joy_snoop: fix DPCM glitch
2026-01-25 Add basic save/restore state support
2026-01-25 Trigger game restore based on execution address
2026-01-26 Implement full core state saving (mapper-agnostic)
2026-01-29 Move state restore to NMI handler
2026-01-31 Add support for new PCB revision
2026-02-02 Simplify power mux and improve audio
2026-02-03 Fix Nametable dump/restore
2026-02-03 Use RTI to restore game state
2026-02-07 Fix pause menu freeze and PPU corruption issues
2026-02-09 Use register for game state
2026-02-10 Add save state interface to mapper bus
2026-02-14 Added mapper registers dump/restore
2026-02-14 Implement state restoration
2026-02-14 Add Open Bus and Bus Conflict support
2026-02-15 Add save state support to CNROM mapper
2026-02-15 Add save state support to MMC1
2026-02-15 Add save state support to VRC6
2026-02-16 Optimize synthesis time by fixing MMC1 FSM inference
2026-02-17 Optimize PRG RAM address path to improve timing closure
2026-02-18 Add VRC6b mapper support and fix WRAM write timing
2026-02-18 Add GitHub Actions workflow
2026-02-19 Remap pins for new PCB layout and add SND_BYPASS
2026-02-20 hw: add parallel map & trace
2026-02-20 hw: fix sdram_tb failure due to multiple drivers
2026-02-20 Add github pages workflow
2026-02-22 pcb: redesign audio circuit with active inverting mixer
2026-02-23 docs: update README with new features and getting started guide
2026-02-23 hw: add support for mappers 155 and 171
2026-02-23 hw: implement bank selection logic for UN1ROM and UNROM mappers
2026-02-23 hw: Add CNROM with copy protection (mapper 185) support
2026-02-23 hw: add basic support for MMC3 mapper
2026-03-04 Add cartridge 3D model
2026-03-04 sw: update FatFs to R0.16
2026-03-05 sw: Clean up dirlist implementation
2026-03-05 hw: Add VRC2/4 mappers implementation
2026-03-07 hw: Add support for mapper 69 and expansion audio
2026-03-10 hw: Refactor PRG CE and IRQ logic in mappers
2026-03-11 Prepare architecture for dynamic multi-bitstream loading
2026-03-14 pcb: Fix USB backpowering to the console through level shifters
2026-03-14 sw: Fix USB VBUS sensing
2026-03-17 hw: Fix reset logic in VRC6 sound
2026-04-06 hw: rework signal assignments for new PCB rev
2026-04-06 sw: fix bootloader VBUS sensing
2026-05-24 ci: automate generation of KiCad manufacturing files

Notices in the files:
board/fcart.kicad_pcb:
Licensed under CERN-OHL-S-2.0
